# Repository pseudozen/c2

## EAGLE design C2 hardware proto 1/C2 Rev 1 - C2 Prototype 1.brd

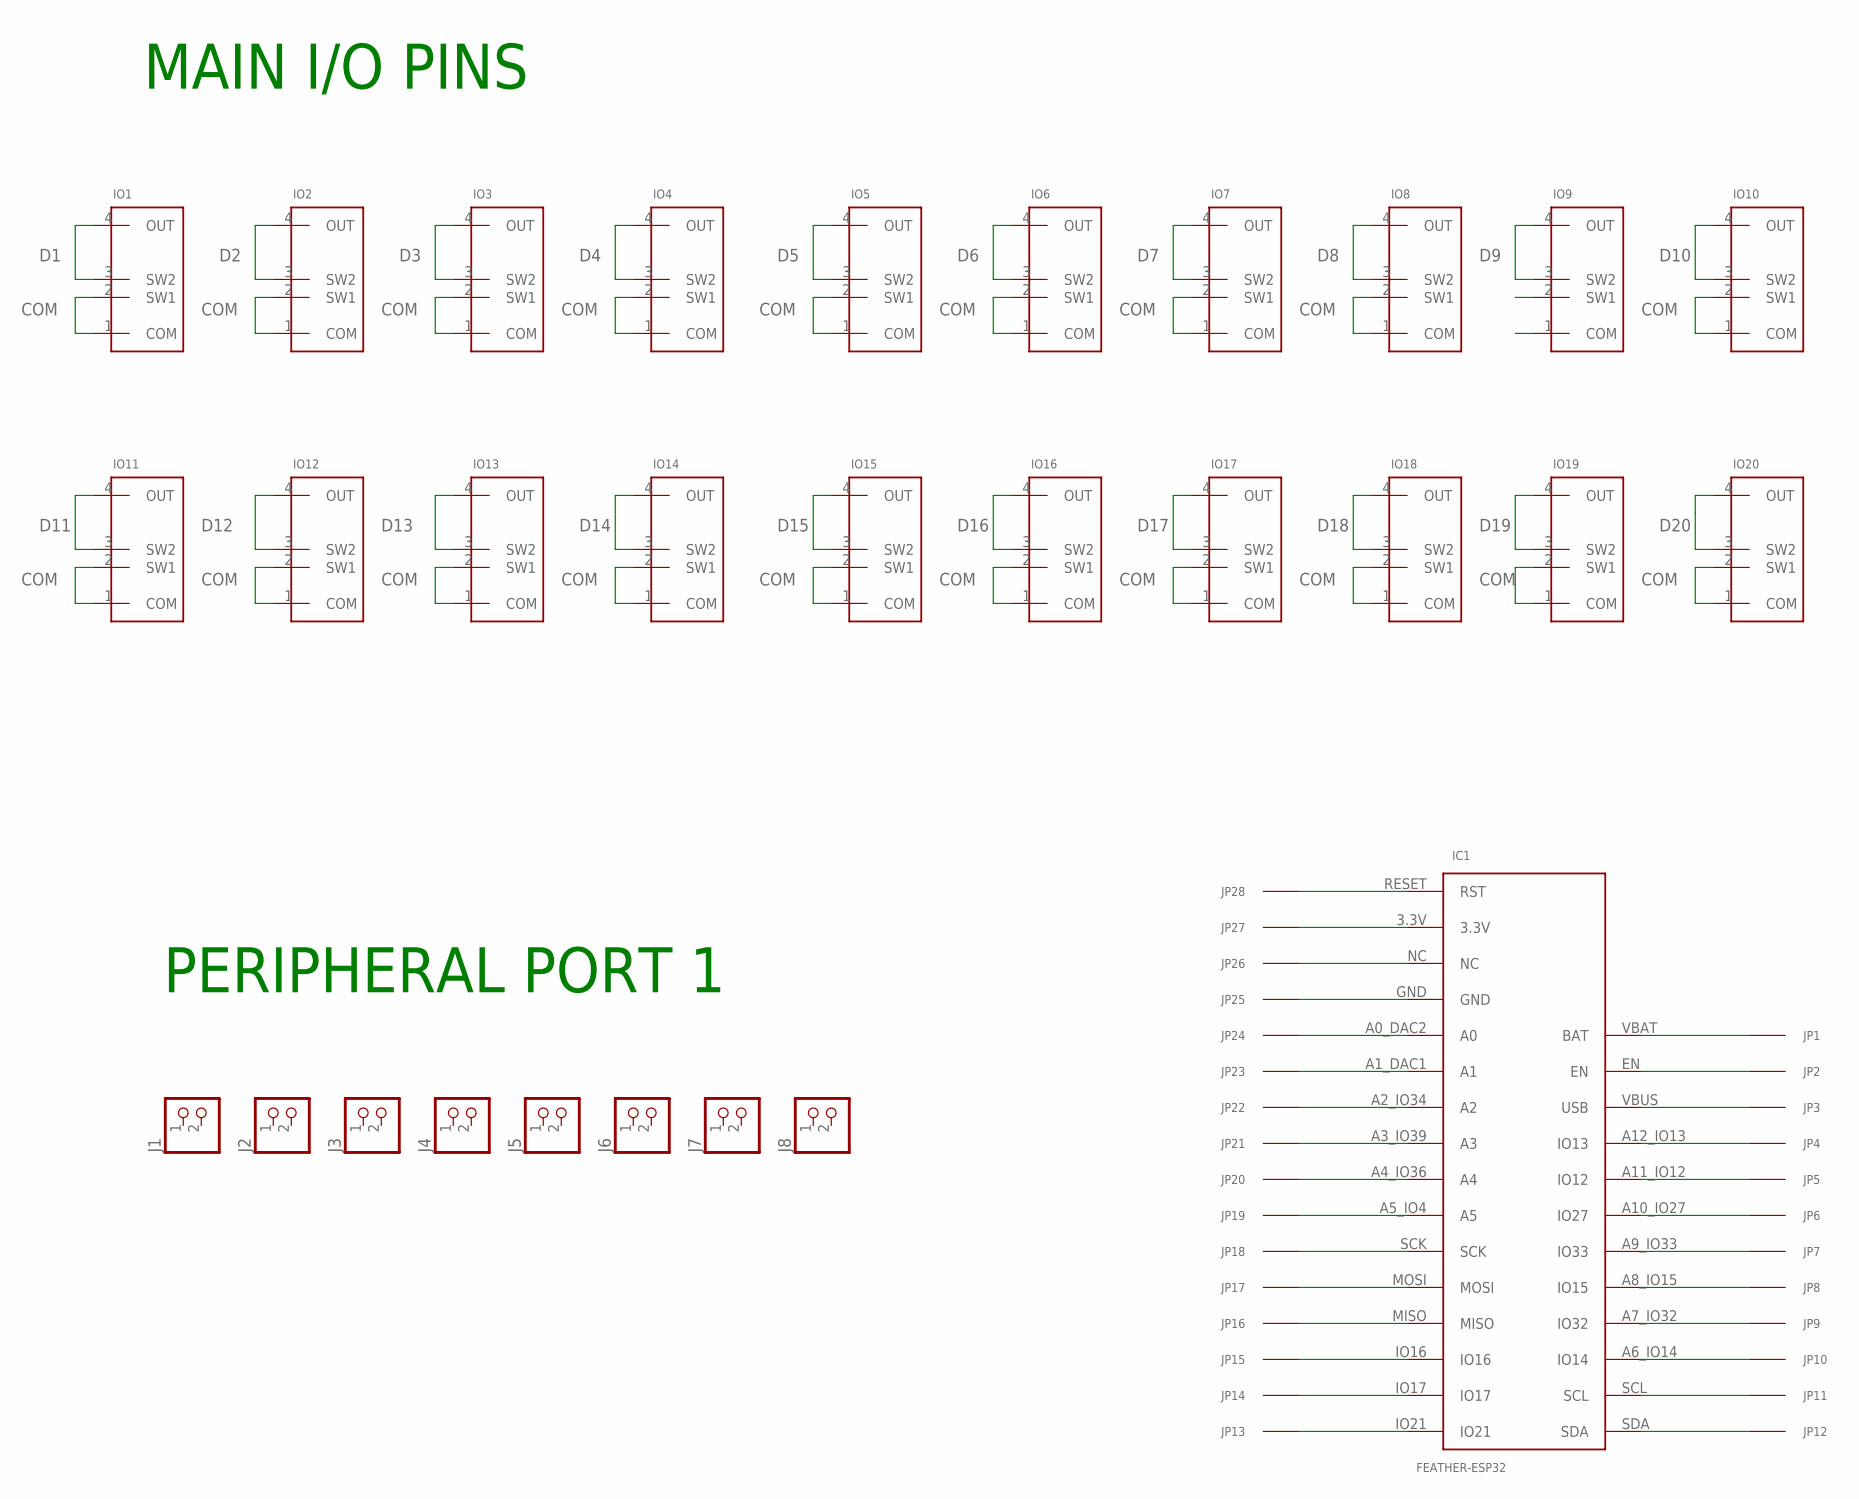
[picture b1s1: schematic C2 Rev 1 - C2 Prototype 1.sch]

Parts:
IC1: FEATHER-ESP32; ESP32_FEATHER
IO1, IO2, IO3, IO4, IO5, IO6, IO7, IO8, IO9, IO10, IO11, IO12, IO13, IO14, IO15, IO16, IO17, IO18, IO19, IO20: C2_IO; C2_IO_VIAS
J1, J2, J3, J4, J5, J6, J7, J8: PINHD-1X2; 1X02
JP1, JP2, JP3, JP4, JP5, JP6, JP7, JP8, JP9, JP10, JP11, JP12, JP13, JP14, JP15, JP16, JP17, JP18, JP19, JP20, JP21, JP22, JP23, JP24, JP25, JP26, JP27, JP28: PROTO_VIA_COMPACT; PROTO_VIA

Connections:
COM: IO1.1 (COM), IO1.2 (SW1), IO2.1 (COM), IO2.2 (SW1), IO3.1 (COM), IO3.2 (SW1), IO4.1 (COM), IO4.2 (SW1), IO5.1 (COM), IO5.2 (SW1), IO6.1 (COM), IO6.2 (SW1), IO7.1 (COM), IO7.2 (SW1), IO8.1 (COM), IO8.2 (SW1), IO9.1 (COM), IO9.2 (SW1), IO10.1 (COM), IO10.2 (SW1), IO11.1 (COM), IO11.2 (SW1), IO12.1 (COM), IO12.2 (SW1), IO13.1 (COM), IO13.2 (SW1), IO14.1 (COM), IO14.2 (SW1), IO15.1 (COM), IO15.2 (SW1), IO16.1 (COM), IO16.2 (SW1), IO17.1 (COM), IO17.2 (SW1), IO18.1 (COM), IO18.2 (SW1), IO19.1 (COM), IO19.2 (SW1), IO20.1 (COM), IO20.2 (SW1)
D1: IO1.3 (SW2), IO1.4 (OUT)
D2: IO2.3 (SW2), IO2.4 (OUT)
D3: IO3.3 (SW2), IO3.4 (OUT)
D4: IO4.3 (SW2), IO4.4 (OUT)
D5: IO5.3 (SW2), IO5.4 (OUT)
D6: IO6.3 (SW2), IO6.4 (OUT)
D7: IO7.3 (SW2), IO7.4 (OUT)
D8: IO8.3 (SW2), IO8.4 (OUT)
D9: IO9.3 (SW2), IO9.4 (OUT)
D10: IO10.3 (SW2), IO10.4 (OUT)
D11: IO11.3 (SW2), IO11.4 (OUT)
D12: IO12.3 (SW2), IO12.4 (OUT)
D13: IO13.3 (SW2), IO13.4 (OUT)
D14: IO14.3 (SW2), IO14.4 (OUT)
D15: IO15.3 (SW2), IO15.4 (OUT)
D16: IO16.3 (SW2), IO16.4 (OUT)
D17: IO17.3 (SW2), IO17.4 (OUT)
D18: IO18.3 (SW2), IO18.4 (OUT)
D19: IO19.3 (SW2), IO19.4 (OUT)
D20: IO20.3 (SW2), IO20.4 (OUT)
unnamed: IC1.RESET (RST), JP28.1
unnamed: IC1.3.3V, JP27.1
unnamed: IC1.NC, JP26.1
unnamed: IC1.GND, JP25.1
unnamed: IC1.A0_DAC2 (A0), JP24.1
unnamed: IC1.A1_DAC1 (A1), JP23.1
unnamed: IC1.A2_IO34 (A2), JP22.1
unnamed: IC1.A3_IO39 (A3), JP21.1
unnamed: IC1.A4_IO36 (A4), JP20.1
unnamed: IC1.A5_IO4 (A5), JP19.1
unnamed: IC1.SCK, JP18.1
unnamed: IC1.MOSI, JP17.1
unnamed: IC1.MISO, JP16.1
unnamed: IC1.IO16, JP15.1
unnamed: IC1.IO17, JP14.1
unnamed: IC1.IO21, JP13.1
unnamed: IC1.SDA, JP12.1
unnamed: IC1.SCL, JP11.1
unnamed: IC1.A6_IO14 (IO14), JP10.1
unnamed: IC1.A7_IO32 (IO32), JP9.1
unnamed: IC1.A8_IO15 (IO15), JP8.1
unnamed: IC1.A9_IO33 (IO33), JP7.1
unnamed: IC1.A10_IO27 (IO27), JP6.1
unnamed: IC1.A11_IO12 (IO12), JP5.1
unnamed: IC1.A12_IO13 (IO13), JP4.1
unnamed: IC1.VBUS (USB), JP3.1
unnamed: IC1.EN, JP2.1
unnamed: IC1.VBAT (BAT), JP1.1

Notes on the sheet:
PERIPHERAL PORT 1
MAIN I/O PINS

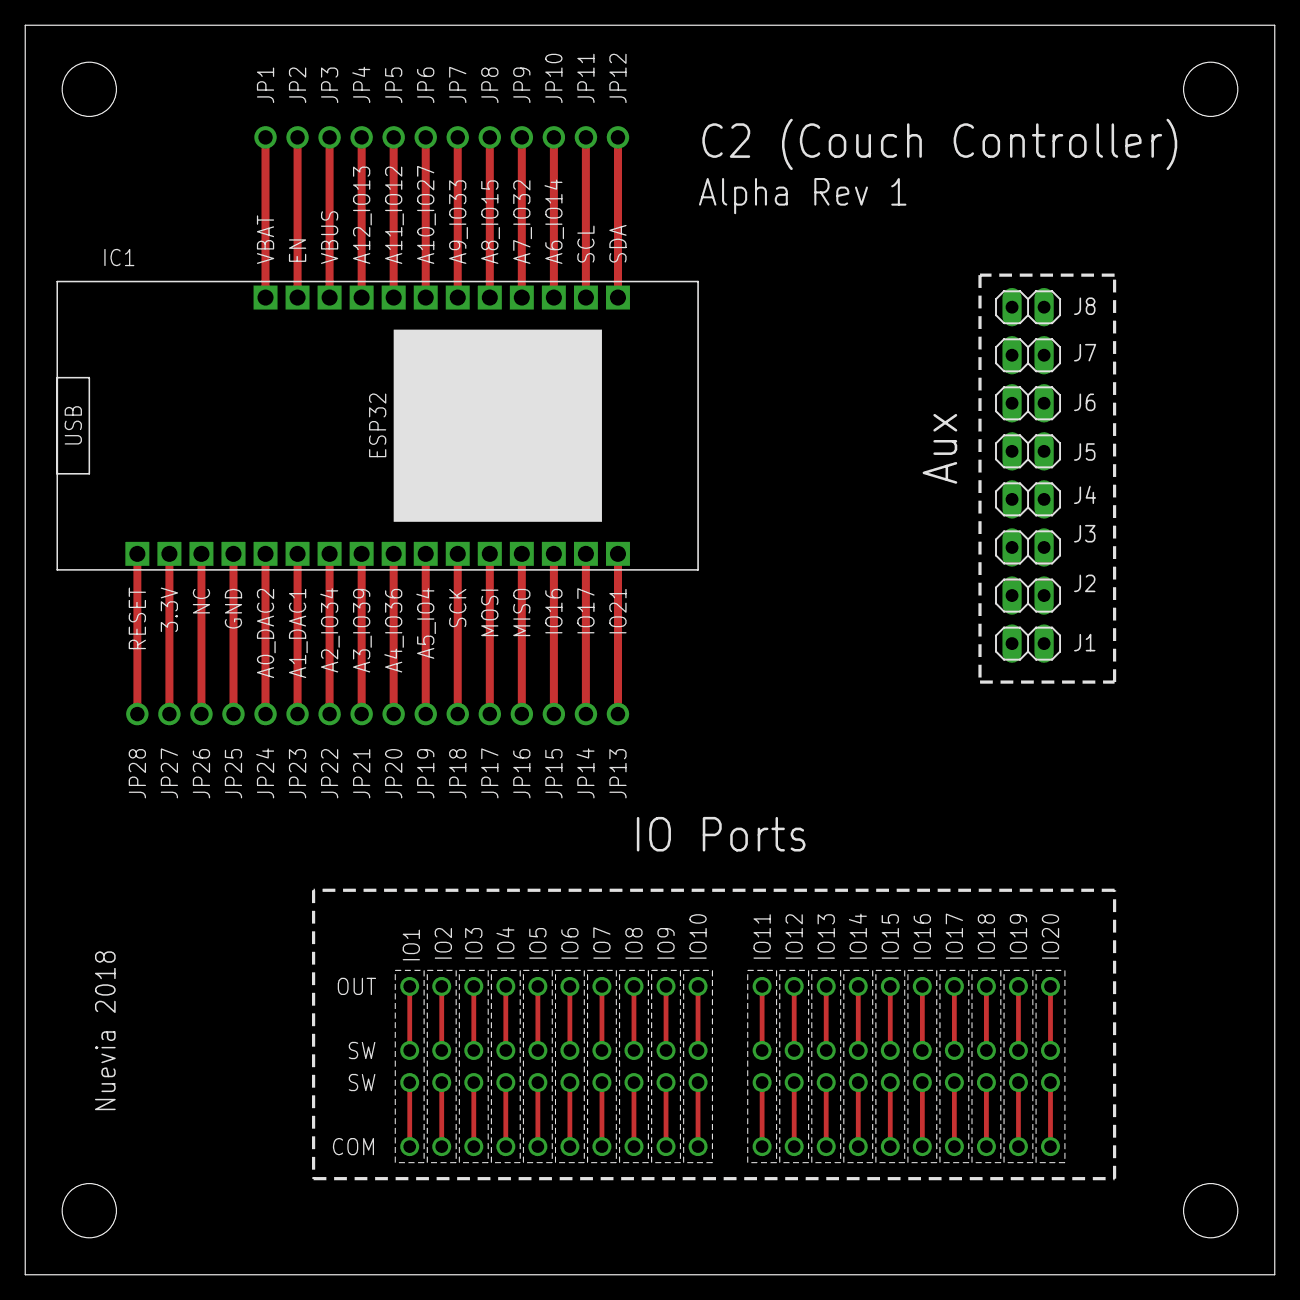
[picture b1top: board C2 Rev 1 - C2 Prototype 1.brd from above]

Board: 2 copper layers, 99.1 x 99.1 mm, 57 parts (0 on the bottom side), 49 nets.

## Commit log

2018-12-13 initial schematic and board for Prototype 1, Rev 1
2018-12-14 Alpha Rev 1, schem and board layed out, ready for routing
2019-01-07 enlarged vias
